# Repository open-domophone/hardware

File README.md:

### Проект печатной 

Проект выполнен в KiCad

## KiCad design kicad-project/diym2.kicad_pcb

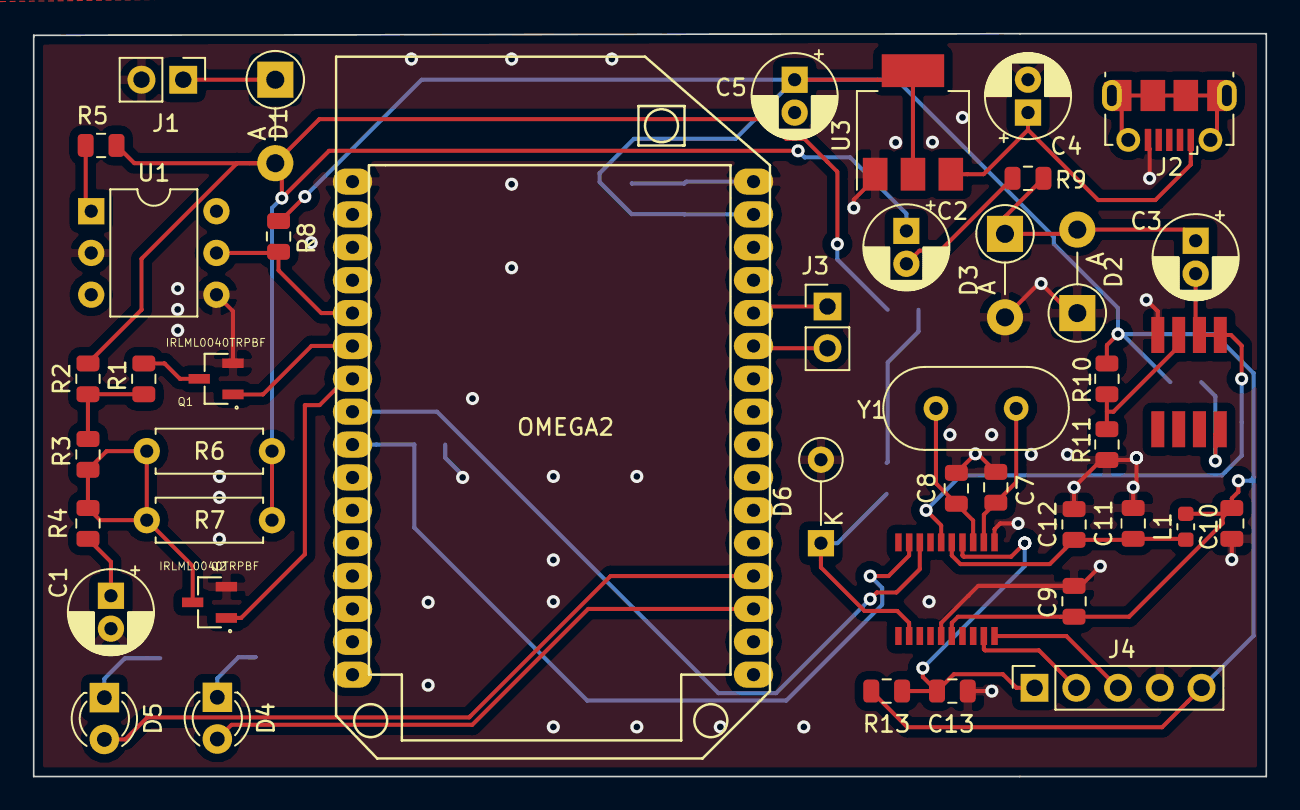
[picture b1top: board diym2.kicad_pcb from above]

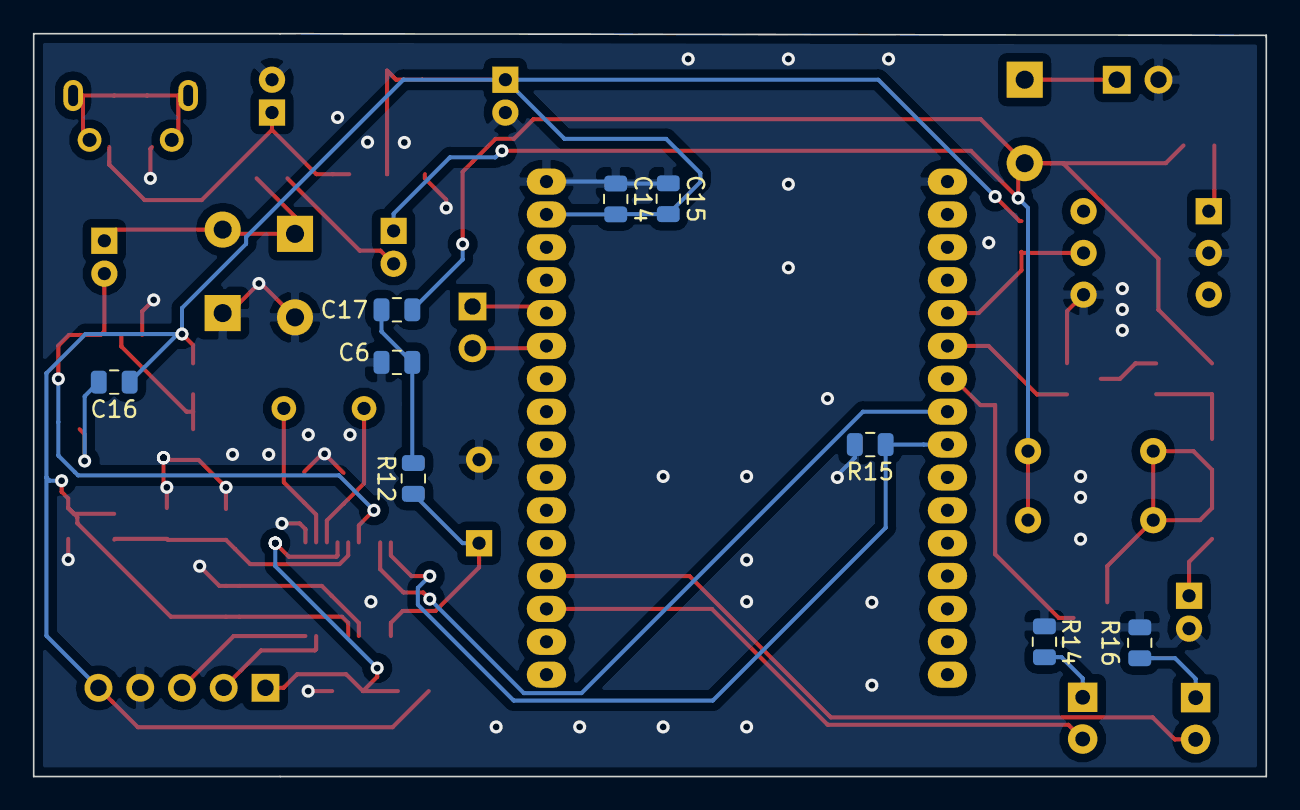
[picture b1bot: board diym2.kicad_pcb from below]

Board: 2 copper layers, 75.0 x 45.2 mm, 52 parts (9 on the bottom side), 34 nets.

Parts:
C1, C4: 10MK; CP_Radial_D5.0mm_P2.00mm
C2, C3: 1MK; CP_Radial_D5.0mm_P2.00mm
C5: 22MK; CP_Radial_D5.0mm_P2.00mm
C6, C14: 0.1мкф; C_0805_2012Metric
C7, C8: 22p; C_0805_2012Metric
C9, C10, C11, C13: 0.1uF; C_0805_2012Metric
C12: 0.01uF; C_0805_2012Metric
C15: 0.01; C_0805_2012Metric
C16, C17: 0.1; C_0805_2012Metric
D1, D2, D3: DIODE; D_DO-41_SOD81_P5.08mm_Vertical_AnodeUp
D4, D5: LED; LED_D3.0mm
D6: D_Zener; D_DO-35_SOD27_P5.08mm_Vertical_KathodeUp
J1: Conn_01x02_Male; PinHeader_1x02_P2.54mm_Vertical
J2: USB_B_Micro; USB_Micro-B_Molex-105017-0001
J3: Conn_01x02_Female; PinHeader_1x02_P2.54mm_Vertical
J4: Conn_01x05_Female; PinSocket_1x05_P2.54mm_Vertical
L1: BLM18HG102SN1D; C_0603_1608Metric
OMEGA2: Onion_Omega2; ONION_OMEGA2
Q1, Q2: IRLML0040TRPBF; SOT95P237X112-3N
R1: 300; R_0805_2012Metric
R2, R3, R4: 220; R_0805_2012Metric
R5: 2K; R_0805_2012Metric
R6, R7: 100; R_Axial_DIN0207_L6.3mm_D2.5mm_P7.62mm_Horizontal
R8, R9, R15: 10K; R_0805_2012Metric
R10, R11, R13: 100K; R_0805_2012Metric
R12: 3.9K; R_0805_2012Metric
R14, R16: 200; R_0805_2012Metric
U1: 4N35; DIP-6_W7.62mm
U2: LM358; SO-8
U3: AMS1117-3.3; SOT-223-3_TabPin2
U4: STM32F030F4Px; TSSOP20
Y1: Crystal; Crystal_HC49-U_Vertical

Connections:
+3V3: C5.1, C9.2, C10.1, C14.2, C15.2, C16.1, J4.5, L1.1, OMEGA2.31, R8.1, R10.1, R13.1, U3.2, U4.16
DOMOPHONE: C2.1, C17.2, D1.2, R2.1, R5.2, R6.1, R7.1
GND: C1.2, C4.2, C5.2, C6.1, C7.1, C8.2, C9.1, C10.2, C11.2, C12.2, C13.1, C14.1, C15.1, D2.1, D3.2, D6.2, J1.2, J2.5, J4.4, OMEGA2.1, OMEGA2.32, Q1.2, Q2.2, R11.2, R14.1, R15.2, R16.1, U1.2, U1.4, U2.4, U3.1, U4.1, U4.15
IS_CALL: OMEGA2.5, R8.2, U1.5
unnamed: C1.1, R4.2
unnamed: C2.2, R9.2
unnamed: C3.1, D2.2, D3.1, R9.1
unnamed: C4.1, J2.1, U3.3
unnamed: C7.2, U4.2, Y1.2
unnamed: C8.1, U4.3, Y1.1
unnamed: C11.1, C12.1, L1.2, U4.5
unnamed: C13.2, J4.1, R13.2, U4.4
unnamed: C16.2, U2.8
unnamed: C6.2, C17.1, R12.2
unnamed: D1.1, J1.1
unnamed: D4.1, R14.2
unnamed: D4.2, OMEGA2.19
unnamed: D5.1, R16.2
unnamed: D5.2, OMEGA2.20
unnamed: J3.1, OMEGA2.28
unnamed: J3.2, OMEGA2.27
unnamed: J4.2, U4.19
unnamed: J4.3, U4.20
unnamed: Q1.3, R1.2
unnamed: Q2.3, R3.2, R4.1, R6.2, R7.2
unnamed: R1.1, R2.2, R3.1
unnamed: R5.1, U1.1
unnamed: R10.2, R11.1, U2.3
OPEN_DOOR: OMEGA2.6, Q1.1
OPEN_PHONE: OMEGA2.7, Q2.1
PWM: D6.1, R12.1, U4.12
SOUND_IN: C3.2, U2.1, U2.2, U4.6
UART_OMEGA_RX: OMEGA2.8, U4.8
UART_OMEGA_TX: OMEGA2.9, R15.1, U4.9

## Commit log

2018-12-23 Create LICENSE
